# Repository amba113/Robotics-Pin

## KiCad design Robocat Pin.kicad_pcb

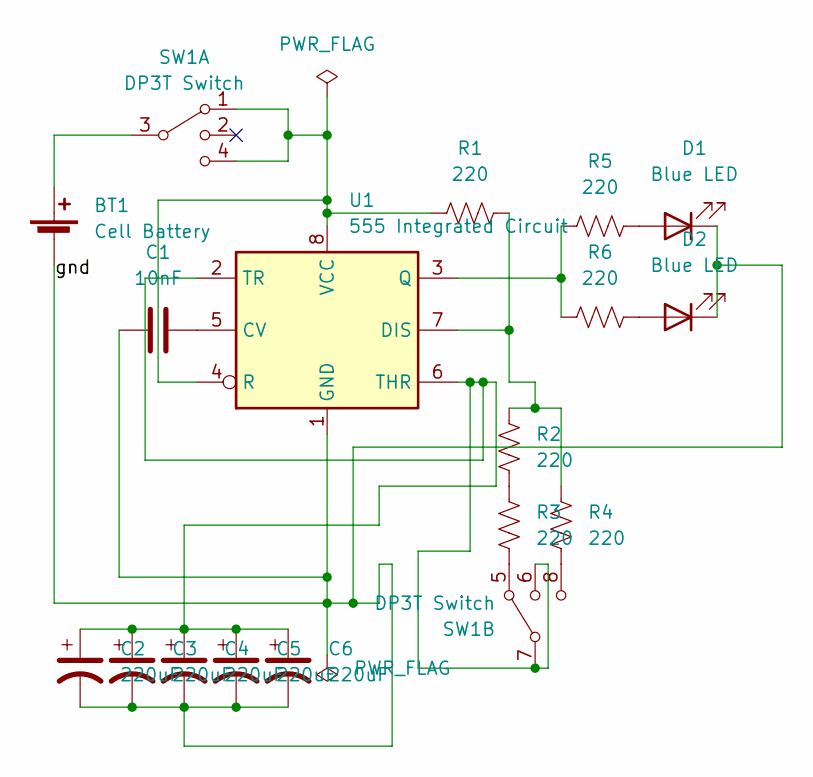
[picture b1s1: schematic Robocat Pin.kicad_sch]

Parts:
BT1: Cell Battery; 2032 Battery Connector; LCSC C964833
C1: 10nF; C_0402_1005Metric; LCSC C60133
C2, C3, C4, C5, C6: 220uF; CP_Elec_6.3x5.4; LCSC C72494
D1, D2: Blue LED; 1206 LED; LCSC C559121
R1, R2, R3, R4, R5, R6: 220; 0603 Resistor; LCSC C22962
SW1: DP3T Switch; DP3T Slide Switch; LCSC C2689537
U1: 555 Integrated Circuit; SOIC - 8 555; LCSC C543060

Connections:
/gnd: BT1.1 (-), C1.1, C2.2, C3.2, C4.2, C5.2, C6.2, D1.1 (K), D2.1 (K), U1.1 (GND)
unnamed: R1.1, SW1.1, SW1.4, U1.4 (R), U1.8 (VCC)
unnamed: BT1.2 (+), SW1.3
unnamed: D1.2 (A), R5.2
unnamed: D2.2 (A), R6.2
unnamed: R2.1, R3.2
unnamed: R3.1, SW1.5
unnamed: R4.1, SW1.8
unnamed: C1.2, U1.5 (CV)
unnamed: R1.2, R2.2, R4.2, U1.7 (DIS)
unnamed: R5.1, R6.1, U1.3 (Q)
unnamed: C2.1, C3.1, C4.1, C5.1, C6.1, SW1.6, SW1.7, U1.2 (TR), U1.6 (THR)

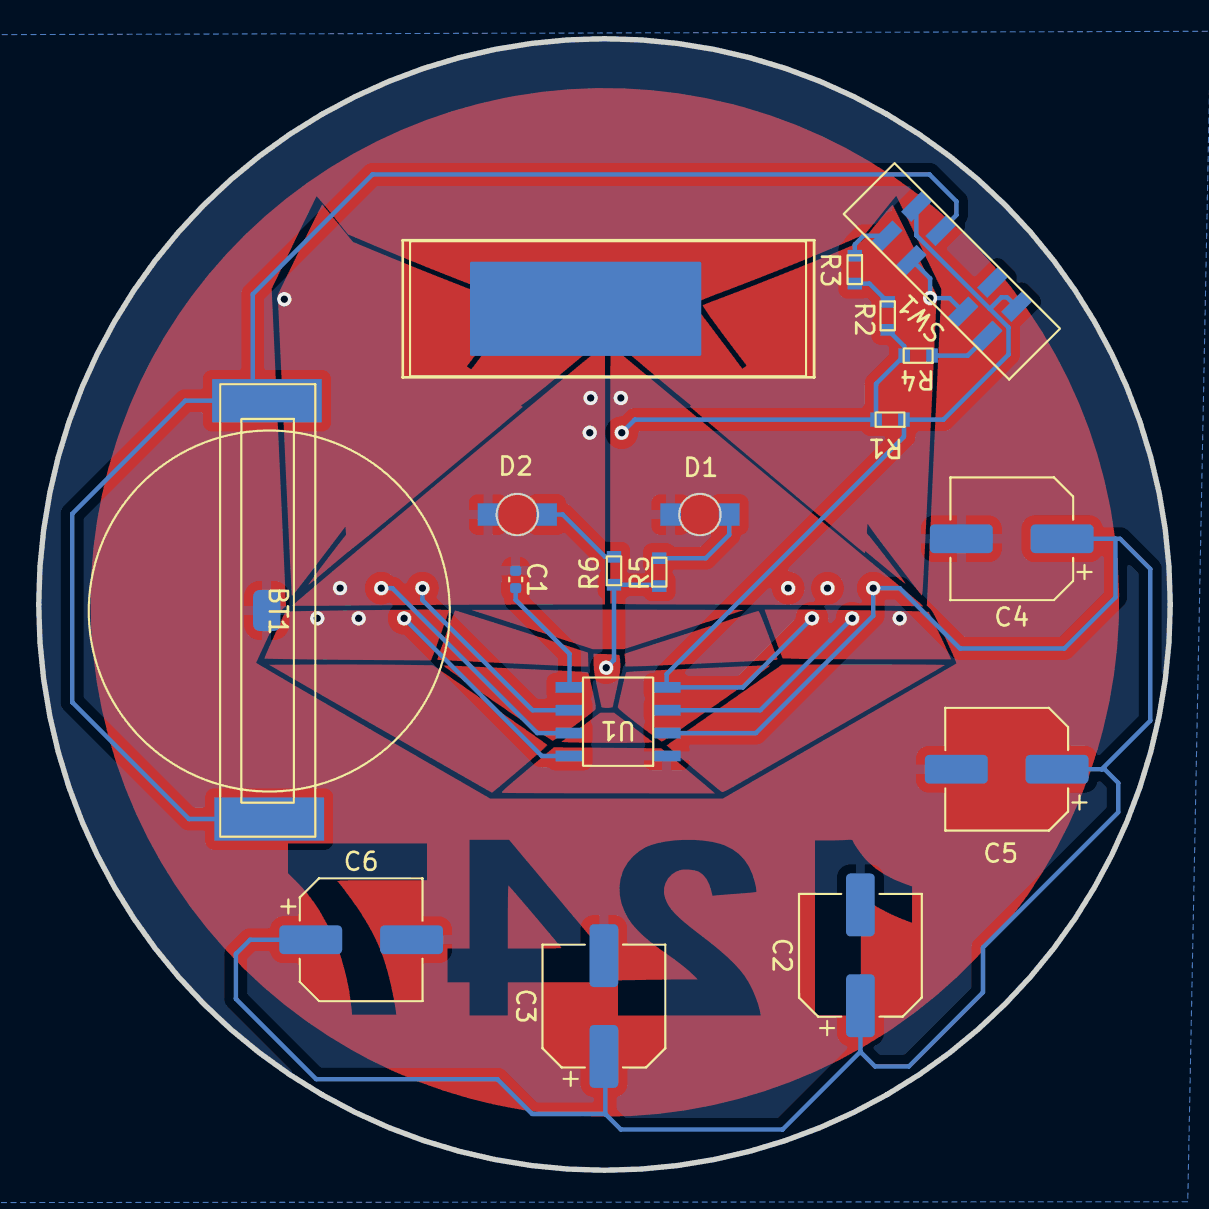
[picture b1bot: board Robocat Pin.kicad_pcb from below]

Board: 4 copper layers, 62.9 x 62.9 mm, 17 parts (17 on the bottom side), 12 nets.

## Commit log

2023-04-20 Initial setup
2023-04-20 Finished schematic and footprint assignments...need to add battery cell holder link then begin pcb design
2023-04-21 Finished schematic and footprint assignments, made falstad version of new circuit design...need to add battery cell holder link then begin pcb design
2023-04-21 Redid the kicad circuit design to fit the update...need to reassign footprints and links, need to find new capacitor
2023-04-21 Made a document with most of the links and footprints of previous circuit design
2023-05-12 Redid circuit, got all footprints done...need to make pcb design
2023-05-23 Made PCB, should be good to go now
2023-05-24 Fixed footprints...need to fix pcb layout (batttery/leds), need to do pcb track
2023-05-25 Rearranged pcb
2023-05-25 Set all the traces
2023-05-25 Fixed robocat background
2023-05-25 Put 3D models for everything, finished pcb layout
2023-05-26 Maybe fixed custom 3d views?
2023-05-31 Worked on bom, working on redoing footprints for missing parts
2023-06-01 Continued working on fixing footprints
2023-06-02 Fixed footprints, parts, pcb
2023-06-02 Something?
2023-06-05 Fixed vias
2023-06-28 Fixed the robocat and pin back areas
2023-06-28 Tried to fix the language of repository
2023-06-28 Undoing change
2023-09-07 Fixed issue that prevented it from blinking, cleaned up PCB design
